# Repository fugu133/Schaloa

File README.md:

# 超小型分光光度計Schaloa
## 概要
浜松ホトニクスのマイクロ分光器[C12880MA](https://www.hamamatsu.com/jp/ja/product/optical-sensors/spectrometers/mini-spectrometer/C12880MA.html)を用いた分光光度計モジュールのハードウェア設計データです．  
本装置を使うと可視領域の分光計測や吸光光度分析がハンディサイズで実現可能です．  
主にCADはEagleとFusionを使用しています．詳しい仕様は[こちら](design_specifications.pdf)    

## 基板のイメージ
### メイン制御基板
分光器や各系の制御，PCとの通信を行います．

### 分光器基板
分光器のブレークアウト基板です．

## 計測デモ
蛍光灯と一般的な白色LEDの放射光スペクトルを計測しました．

### 蛍光灯
405nm，436nm，546nm及び577nm付近に鋭いピークが見られます．  
これらは蛍光灯の発光源である水銀の原子スペクトルと一致しています．  
この光を管内の蛍光体に照射すると蛍光により白色光が作成されます．

### 白色LED
頂点が過剰露出により潰れていますが，440nm付近に鋭いピークが見られます．  
これはパッケージ内部の青色LEDによる光だと考えられます．所謂ブルーライトです．  
また550nm-560nm付近を中心に広いピークを確認できます．  
これは黄色系の蛍光体の蛍光だと考えられます．白色LEDはこのようにして白色光を作成します．

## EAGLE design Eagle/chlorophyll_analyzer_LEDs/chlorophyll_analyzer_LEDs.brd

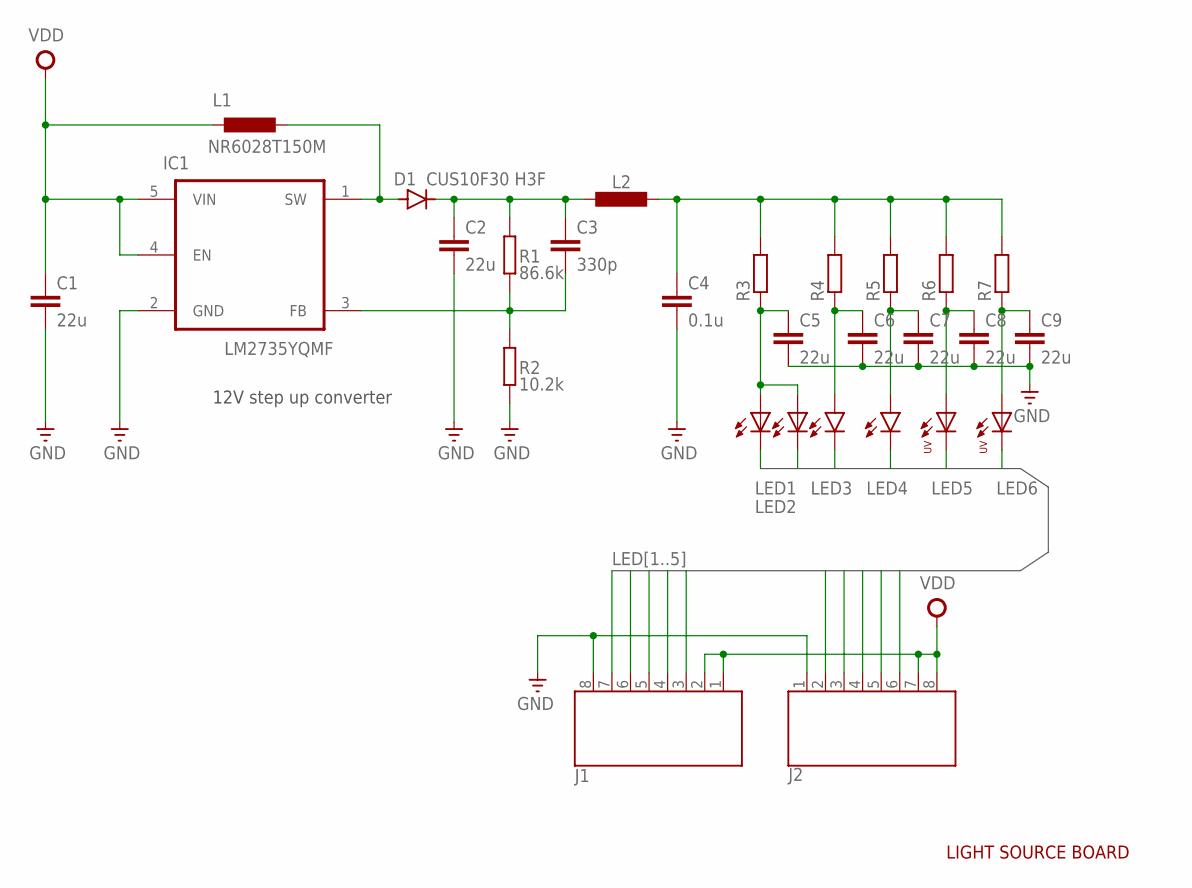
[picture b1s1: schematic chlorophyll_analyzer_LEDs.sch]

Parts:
C1, C2, C5, C6, C7, C8, C9: 22u; C0603K
C3: 330p; C0603K
C4: 0.1u; C0603K
D1: CUS10F30 H3F; SOD323-W
IC1: LM2735YQMF; SOT65P285X120-5N
J1, J2: 687108183722
L1: NR6028T150M; IND_TAIYO_NR6028
L2: INDUCOR2012; SMD2012
LED1, LED2: L130-S1S0-3030509506-0000003S-000015080003000W21; LED_L130-5080003000W21
LED3, LED4: LEDCHIPLED_1206; CHIPLED_1206
LED5, LED6: ELUA2016OGB-P8090Q53038020-VA1M; ELUA2016OGB0.08
R1: 86.6k; SMD1608
R2: 10.2k; SMD1608
R3, R4, R5, R6, R7: R-EU_R0805; R0805

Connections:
AVOUT_12V: C4.1, L2.1, R3.2, R4.2, R5.2, R6.2, R7.2
GND: C1.2, C2.2, C4.2, C5.2, C6.2, C7.2, C8.2, C9.2, IC1.2 (GND), J1.8 (1), J2.1 (8), R2.1
LED1: J1.3 (6), J2.6 (3), LED1.C, LED2.C
LED2: J1.4 (5), J2.5 (4), LED3.C
LED3: J1.5 (4), LED4.C
LED4: J1.6 (3), J2.3 (6), J2.4 (5), LED5.C (C1)
LED5: J1.7 (2), J2.2 (7), LED6.C (C1)
unnamed: C5.1, LED1.A, LED2.A, R3.1
unnamed: C6.1, LED3.A, R4.1
unnamed: C7.1, LED4.A, R5.1
unnamed: C9.1, LED6.A (A1), R7.1
unnamed: C8.1, LED5.A (A1), R6.1
unnamed: C2.1, C3.1, D1.C, L2.2, R1.2
unnamed: D1.A, IC1.1 (SW), L1.1
unnamed: C3.2, IC1.3 (FB), R1.1, R2.2
VDD: C1.1, IC1.4 (EN), IC1.5 (VIN), J1.1 (8), J1.2 (7), J2.7 (2), J2.8 (1), L1.2

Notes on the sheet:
12V step up converter
LIGHT SOURCE BOARD

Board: 2 copper layers, 28 parts (21 on the bottom side), 16 nets, no tracks yet.

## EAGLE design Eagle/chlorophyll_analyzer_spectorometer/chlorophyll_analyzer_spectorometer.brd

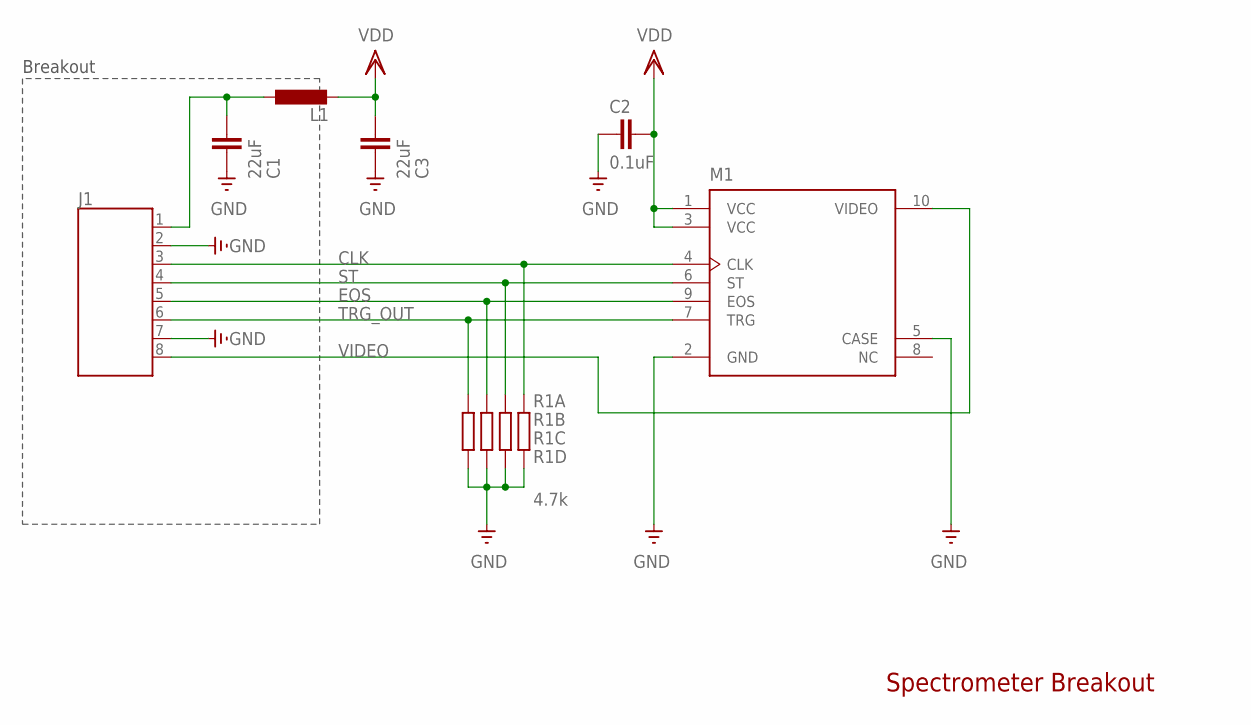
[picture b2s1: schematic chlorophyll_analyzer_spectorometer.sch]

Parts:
C1, C3: 22uF; C0603K
C2: 0.1uF; C0603K
J1: 687108183722
L1: INDUCOR1608; SMD1608
M1: C12880MA
R1: 4.7k; RESCAXS80P320X160X60-8N

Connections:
CLK: J1.3 (6), M1.4 (CLK), R1.5 (2)
EOS: J1.5 (4), M1.9 (EOS), R1.7 (2)
GND: C1.2, C2.2, C3.2, J1.2 (7), J1.7 (2), M1.2 (GND), M1.5 (CASE), R1.1, R1.2 (1), R1.3 (1), R1.4 (1)
unnamed: C1.1, J1.1 (8), L1.1
ST: J1.4 (5), M1.6 (ST), R1.6 (2)
TRG_OUT: J1.6 (3), M1.7 (TRG), R1.8 (2)
VDD: C2.1, C3.1, L1.2, M1.1 (VCC), M1.3 (VCC)
VIDEO: J1.8 (1), M1.10 (VIDEO)

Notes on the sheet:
Breakout
Spectrometer Breakout

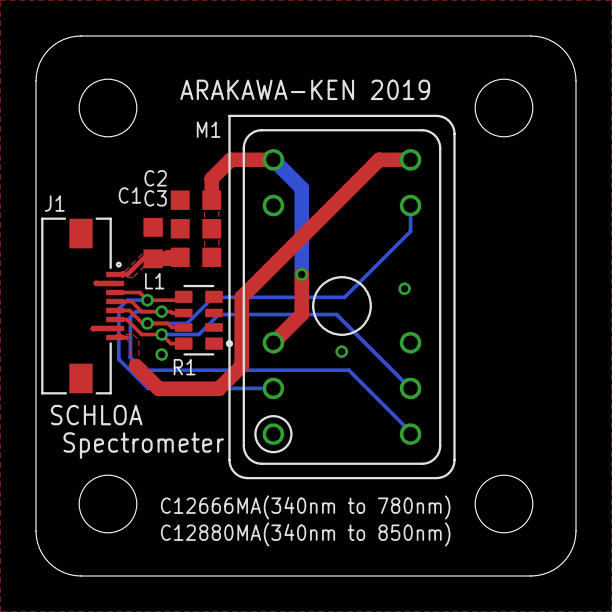
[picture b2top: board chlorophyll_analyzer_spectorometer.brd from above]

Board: 2 copper layers, 30.0 x 30.0 mm, 7 parts (0 on the bottom side), 8 nets.

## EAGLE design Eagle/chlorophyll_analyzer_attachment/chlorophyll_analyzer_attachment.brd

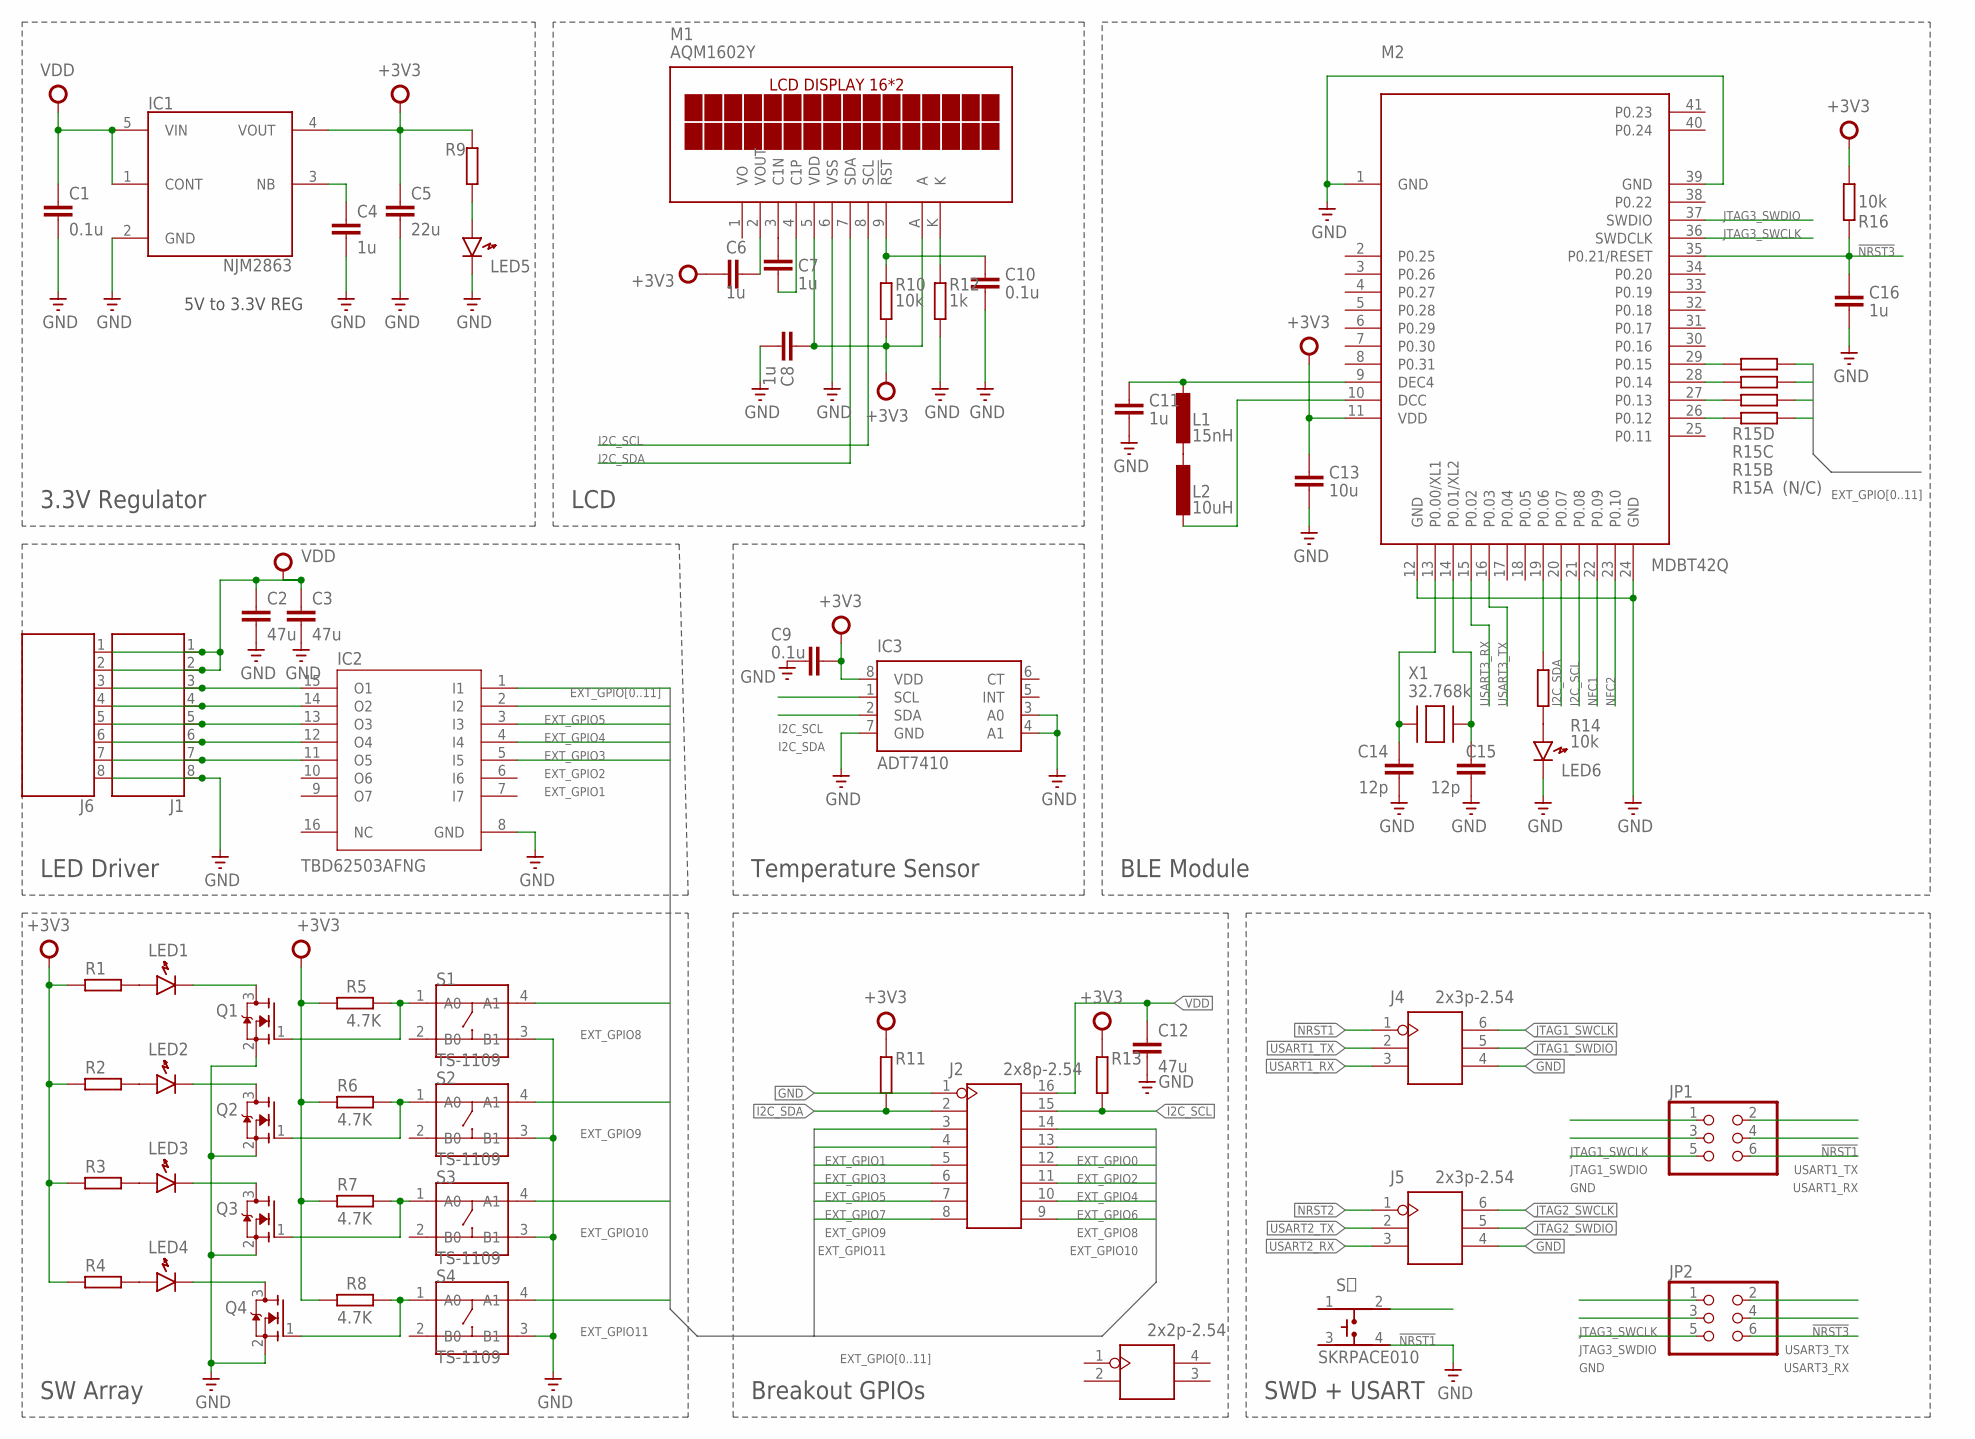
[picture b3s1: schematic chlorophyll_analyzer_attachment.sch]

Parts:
C1, C9, C10: 0.1u; C0603K
C2, C3, C12: 47u; C1206
C4, C6, C7, C8, C11, C16: 1u; C0603K
C5: 22u; C0603K
C13: 10u; C0603K
C14, C15: 12p; C0603K
IC1: NJM2863; SOT-23-5
IC2: TBD62503AFNG; SSOP16-P-225-0.65B
IC3: ADT7410; SOIC8
J1, J6: 687108183722
J2: 2x8p-2.54; H2X8-2.54
J3: 2x2p-2.54; H2X2-2.54
J4, J5: 2x3p-2.54; H2X3-2.54
JP1, JP2: PINHD-2X3; 2X03
L1: 15nH; SMD1608
L2: 10uH; SMD1608
LED1, LED2, LED3, LED4, LED5, LED6: LED1608
M1: AQM1602Y
M2: MDBT42Q
Q1, Q2, Q3, Q4: MOSFET-NREFLOW; SOT23
R1, R2, R3, R4, R9, R11, R13: RESISTOR1608; SMD1608
R5, R6, R7, R8: 4.7K; SMD1608
R10, R14, R16: 10k; SMD1608
R12: 1k; SMD1608
R15: (N/C); RESCAXS80P320X160X60-8N
S1, S2, S3, S4: TS-1109; SW4-6.0X6.0X5.0MM
S５: SKRPACE010; SW_SKRPACE010
X1: 32.768k; XTAL3215

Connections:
!NRST1: J4.1, JP1.2, S５.2
!NRST2: J5.1
!NRST3: C16.1, JP2.2, M2.35 (P0.21/RESET), R16.1
+3V3: C5.1, C6.1, C8.2, C9.1, C13.1, IC1.4 (VOUT), IC3.8 (VDD), M1.5 (VDD), M1.A, M2.11 (VDD), R1.1, R2.1, R3.1, R4.1, R5.1, R6.1, R7.1, R8.1, R9.1, R10.2, R11.1, R13.1, R16.2
EXT_GPIO0: J2.14
EXT_GPIO1: IC2.5 (I5), J2.3
EXT_GPIO2: IC2.4 (I4), J2.13
EXT_GPIO3: IC2.3 (I3), J2.4
EXT_GPIO4: IC2.2 (I2), J2.12
EXT_GPIO5: IC2.1 (I1), J2.5
EXT_GPIO6: J2.11
EXT_GPIO7: J2.6
EXT_GPIO8: J2.10, R15.8 (2), S1.4 (A1)
EXT_GPIO9: J2.7, R15.7 (2), S2.4 (A1)
EXT_GPIO10: J2.9, R15.6 (2), S3.4 (A1)
EXT_GPIO11: J2.8, R15.5 (2), S4.4 (A1)
GND: C1.2, C2.2, C3.2, C4.2, C5.2, C8.1, C9.2, C10.2, C11.2, C12.2, C13.2, C14.2, C15.2, C16.2, IC1.2 (GND), IC2.8 (GND), IC3.3 (A0), IC3.4 (A1), IC3.7 (GND), J1.8 (1), J2.1, J4.4, J5.4, J6.8 (1), JP1.5, JP2.5, LED5.K, LED6.K, M1.6 (VSS), M2.1 (GND), M2.12 (GND), M2.24 (GND), M2.39 (GND), Q1.2 (S), Q2.2 (S), Q3.2 (S), Q4.2 (S), R12.2, S1.3 (B1), S2.3 (B1), S3.3 (B1), S4.3 (B1), S５.4
I2C_SCL: IC3.1 (SCL), J2.15, M1.8 (SCL), M2.21 (P0.08), R13.2
I2C_SDA: IC3.2 (SDA), J2.2, M1.7 (SDA), M2.20 (P0.07), R11.2
JTAG1_SWCLK: J4.6, JP1.1
JTAG1_SWDIO: J4.5, JP1.3
JTAG2_SWCLK: J5.6
JTAG2_SWDIO: J5.5
JTAG3_SWCLK: JP2.1, M2.36 (SWDCLK)
JTAG3_SWDIO: JP2.3, M2.37 (SWDIO)
unnamed: C6.2, M1.2 (VOUT)
unnamed: C7.2, M1.3 (C1N)
unnamed: C7.1, M1.4 (C1P)
unnamed: C4.1, IC1.3 (NB)
unnamed: LED5.A, R9.2
unnamed: C10.1, M1.9 (!RST), R10.1
unnamed: M1.K, R12.1
unnamed: Q1.1 (G), R5.2, S1.1 (A0)
unnamed: Q2.1 (G), R6.2, S2.1 (A0)
unnamed: Q3.1 (G), R7.2, S3.1 (A0)
unnamed: Q4.1 (G), R8.2, S4.1 (A0)
unnamed: L2.2, M2.10 (DCC)
unnamed: M2.19 (P0.06), R14.2
unnamed: C11.1, L1.1, M2.9 (DEC4)
unnamed: LED6.A, R14.1
unnamed: LED1.A, R1.2
unnamed: LED2.A, R2.2
unnamed: LED3.A, R3.2
unnamed: LED4.A, R4.2
unnamed: LED4.K, Q4.3 (D)
unnamed: LED3.K, Q3.3 (D)
unnamed: LED2.K, Q2.3 (D)
unnamed: LED1.K, Q1.3 (D)
unnamed: C14.1, M2.13 (P0.00/XL1), X1.P$1
unnamed: L1.2, L2.1
unnamed: C15.1, M2.14 (P0.01/XL2), X1.P$2
unnamed: M2.26 (P0.12), R15.1
unnamed: M2.27 (P0.13), R15.2 (1)
unnamed: M2.28 (P0.14), R15.3 (1)
unnamed: M2.29 (P0.15), R15.4 (1)
unnamed: IC2.15 (O1), J1.3 (6), J6.3 (6)
unnamed: IC2.14 (O2), J1.4 (5), J6.4 (5)
unnamed: IC2.13 (O3), J1.5 (4), J6.5 (4)
unnamed: IC2.12 (O4), J1.6 (3), J6.6 (3)
unnamed: IC2.11 (O5), J1.7 (2), J6.7 (2)
NFC1: M2.22 (P0.09)
NFC2: M2.23 (P0.10)
USART1_RX: J4.3, JP1.6
USART1_TX: J4.2, JP1.4
USART2_RX: J5.3
USART2_TX: J5.2
USART3_RX: JP2.6, M2.15 (P0.02)
USART3_TX: JP2.4, M2.16 (P0.03)
VDD: C1.1, C2.1, C3.1, C12.1, IC1.1 (CONT), IC1.5 (VIN), J1.1 (8), J1.2 (7), J2.16, J6.1 (8), J6.2 (7)

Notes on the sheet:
SWD + USART
Breakout GPIOs
5V to 3.3V REG
SW Array
LED Driver
Temperature Sensor
BLE Module
3.3V Regulator
LCD

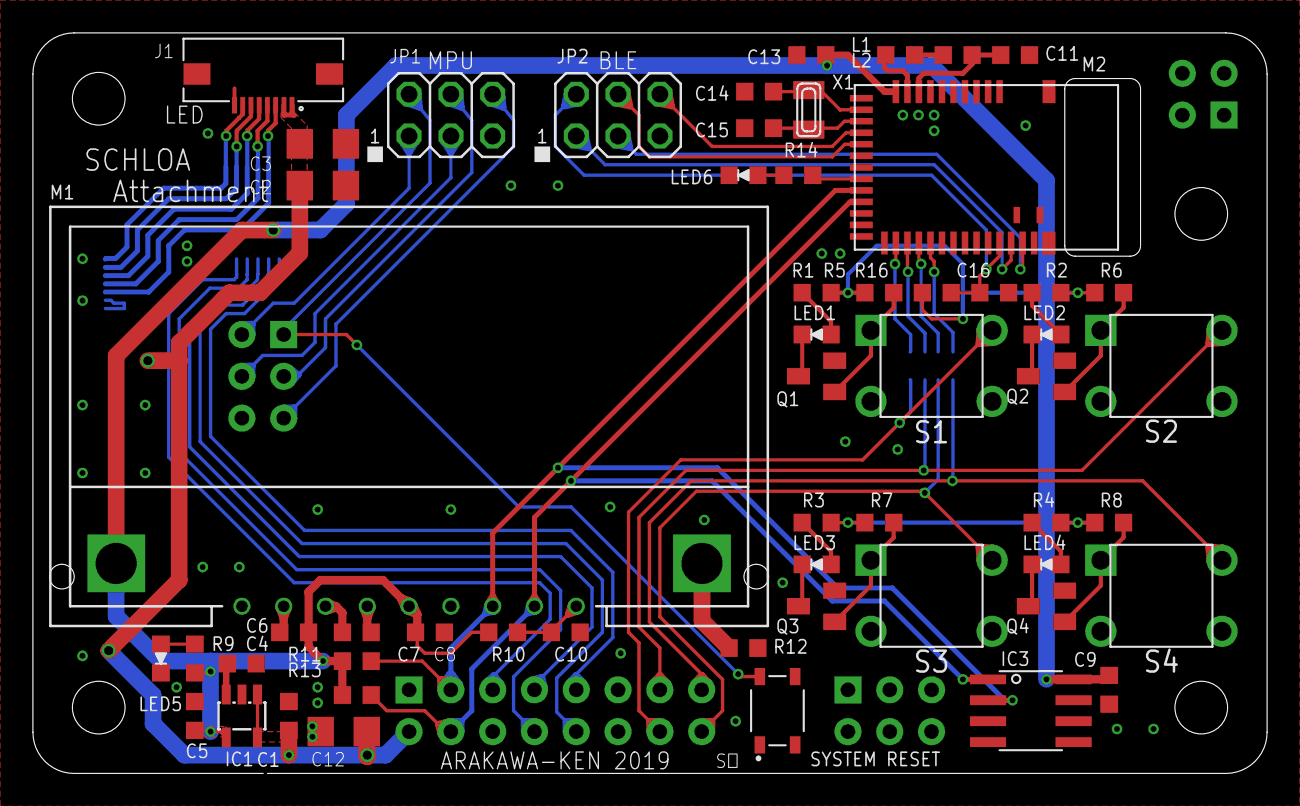
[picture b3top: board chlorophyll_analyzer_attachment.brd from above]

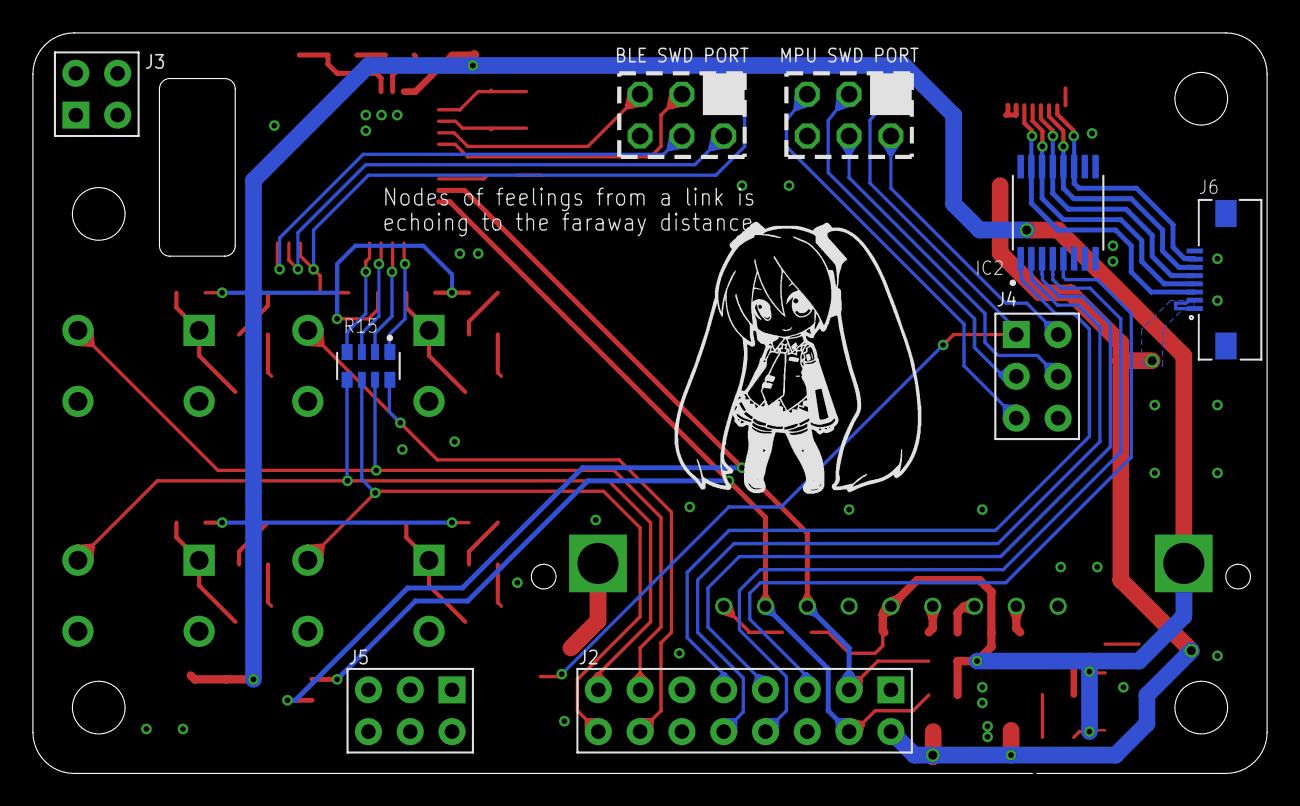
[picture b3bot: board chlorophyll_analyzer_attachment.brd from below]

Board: 2 copper layers, 75.0 x 45.0 mm, 63 parts (7 on the bottom side), 59 nets.

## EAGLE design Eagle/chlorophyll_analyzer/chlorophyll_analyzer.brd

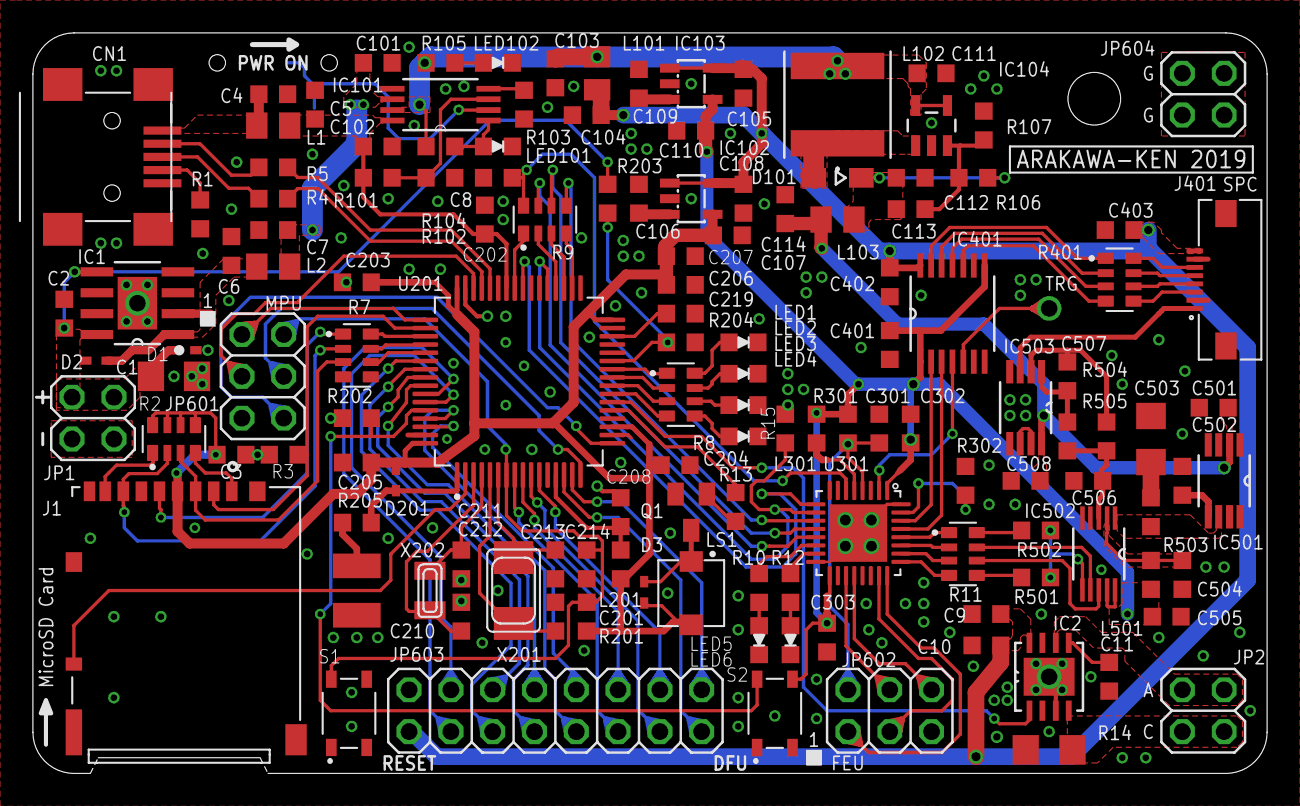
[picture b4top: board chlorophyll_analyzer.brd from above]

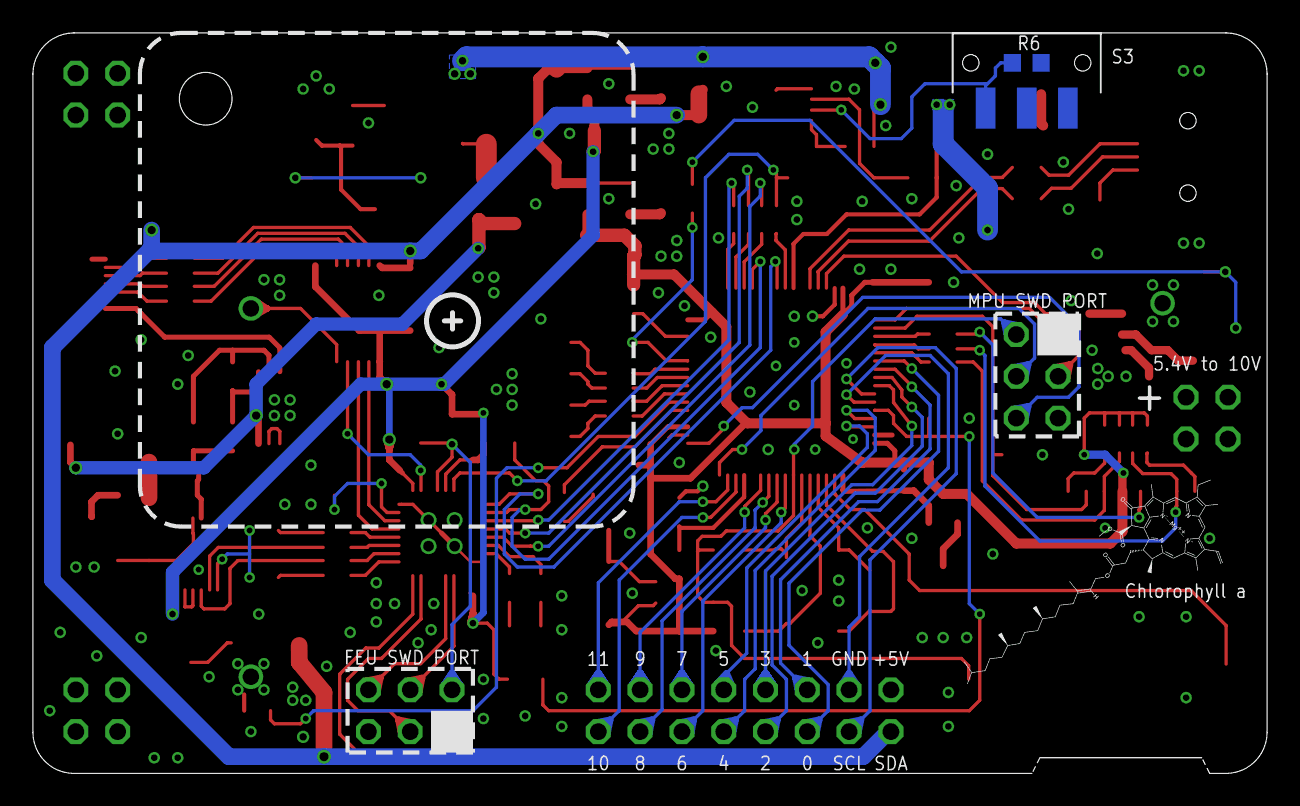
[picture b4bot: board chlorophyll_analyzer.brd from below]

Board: 2 copper layers, 75.0 x 45.0 mm, 137 parts (2 on the bottom side), 130 nets.

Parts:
C1, C503: 47u; C1206
C2, C106, C109, C501, C502, C504, C505: 1u; C0603K
C3, C4, C6, C9, C101, C102, C103, C104, C107, C110, C111, C112: 22u; C0603K
C5, C7, C10, C105, C108, C114, C201, C202, C203, C204, C205, C206, C208, C301, C302, C303, C401, C402, C508: 0.1u; C0603K
C8: 20p; C0603K
C11: 47n; C0603K
C113: 330p; C0603K
C207, C219: 4.7u; C0603K
C210: CPH3225A(11mF); C1210K
C211, C212: 12p; C0603K
C213, C214: 18p; C0603K
C403: 22uF; C0603K
C506, C507: 2.4n; C0603K
CN1: USB-MINIB
D1, D2, D3, D201: RB520S-30; SOD523
D101: CUS10F30 H3F; SOD323-W
IC1: BD50HC5WEFJ; HTSOP-J8
IC2: TL4242DRJR; SON80P410X410X80-9N
IC101: TPS2113PW; SOP65P640X120-8N
IC102, IC103: NJM2863; SOT-23-5
IC104: LM2735YQMF; SOT65P285X120-5N
IC401: TXB0104PWR; SOP65P640X120-14N
IC501: REF5050AIDGKT; SOP65P490X110-8N
IC502: ADS8866IDGS; SOP50P490X110-10N
IC503: OPA2388IDGKT; SOP65P490X110-9N
J1: DM3AT-SF-PEJM5; HRS_DM3AT-SF-PEJM5
J401: 687108183722
JP1, JP2, JP604: 2X02
JP601, JP602: 2X03
JP603: 2X08
L1, L2, L101, L103: SMD2012
L102: NR6028T150M; IND_TAIYO_NR6028
L201, L301, L501: SMD1608
LED1, LED2, LED3, LED4, LED5, LED6, LED101, LED102: LED1608
LS1: SMT-0440-T-R; XDCR_SMT-0440-T-R
Q1: SOT23
R1, R3, R15: 100k; SMD1608
R2: 22k; RESCAXS80P320X160X60-8N
R4, R5: 10; SMD1608
R6, R502: 0(N/C); SMD1608
R7, R9, R11, R401: 20; RESCAXS80P320X160X60-8N
R8: 4.7k; RESCAXS80P320X160X60-8N
R10, R12, R104, R105, R204: 4.7k; SMD1608
R13, R101: 1k; SMD1608
R14: R1206
R102, R201, R202, R203, R301, R302: 10k; SMD1608
R103: 400; SMD1608
R106: 86.6k; SMD1608
R107: 10.2k; SMD1608
R205: 100; SMD1608
R501, R503: 0; SMD1608
R504, R505: 20k; SMD1608
S1, S2: SKRPACE010; SW_SKRPACE010
S3: JS102011SAQN; SW_JS102011SAQN
U201: STM32F446RET6; QFP50P1200X1200X160-64N
U301: STM32L432KCU6; QFN50P500X500X60-33N
X201: 8.0MHz; NX5032
X202: 32.768k; XTAL3215

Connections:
!FEU_NRST: C301.1, JP602.2, R301.2, U301.4
!FEU_SPI_CS: R15.1, U201.37, U301.10
!MPU_NRST: C201.2, JP601.2, R201.2, S1.2, U201.7
!SD_CDETECT: J1.SWA, U201.2
!SD_SPI_CS: J1.2, R3.1, U201.50
+3V3A: C3.1, C107.1, C203.1, C204.1, C205.1, C206.1, C207.1, D3.C, D201.A, IC102.4, J1.4, L201.1, LS1.2, R2.5, R2.6, R2.7, R2.8, R201.1, U201.19, U201.32, U201.48, U201.64
+3V3C: C110.1, C302.1, C303.1, C401.2, C505.1, IC103.4, IC401.1, IC401.8, IC502.9, IC502.10, L301.1, L501.1, R301.1, S2.4, U301.1, U301.17
+5VA: C103.1, C111.1, IC101.7, IC104.4, IC104.5, L101.2, L102.2, R104.1, R105.1
+5VD: C9.2, C10.2, C104.1, C105.1, C108.1, C402.1, C403.1, IC2.8, IC102.1, IC102.5, IC103.1, IC103.5, IC401.14, J401.8, JP603.1, L101.1
+12V: C114.1, C501.1, C508.1, IC501.2, IC503.8, L103.1
ADC_AT_TRG: R11.8, R502.1
ADC_MN_TRG: R11.5, R501.1
ADC_SPI_MISO: IC502.7, R11.7
ADC_SPI_SCLK: IC502.8, R11.6
ADC_UNIT:ADC_CTRG: IC502.6, R501.2, R502.2
ADC_UNIT:N$1: C503.2, R503.1
ADC_UNIT:N$2: IC503.6, IC503.7
ADC_UNIT:N$3: C504.1, IC502.2, L501.2
ADC_UNIT:N$25: C506.1, IC502.3, R504.1, R505.1
ADC_UNIT:N$26: C507.1, IC503.1, R504.2
ADC_UNIT:N$30: C507.2, IC503.2, R505.2
ADC_UNIT:N$34: C502.1, IC501.5
ADC_UNIT:VREF: IC501.6, IC502.1, R503.2
EXT_GPIO0: JP603.5, U201.54
EXT_GPIO1: JP603.6, U201.55
EXT_GPIO2: JP603.7, U201.56
EXT_GPIO3: JP603.8, U201.57
EXT_GPIO4: JP603.9, U201.61
EXT_GPIO5: JP603.10, U201.62
EXT_GPIO6: JP603.11, U201.8
EXT_GPIO7: JP603.12, U201.9
EXT_GPIO8: JP603.13, U201.10
EXT_GPIO9: JP603.14, U201.11
EXT_GPIO10: JP603.15, U201.14
EXT_GPIO11: JP603.16, U201.15
FEU_MCLK: C8.1, R9.8, U301.6
FEU_RX: JP602.6, U301.20
FEU_SPI_BUSY: U201.40, U301.9
FEU_SPI_SCLK: R9.5, U301.11
FEU_ST_LED0: R10.1, U301.14
FEU_ST_LED1: R12.1, U301.15
FEU_SWCLK: JP602.1, U301.24
FEU_SWDIO: JP602.3, U301.23
FEU_TX: JP602.4, U301.19
FPU_SPI_MISO: R9.6, U301.12
FPU_SPI_MOSI: R9.7, U301.13
FRONT_END_UNIT:N$1: L301.2, U301.5
FRONT_END_UNIT:N$10: R302.1, U301.31
GND: C1.2, C2.2, C3.2, C4.2, C5.2, C6.2, C7.2, C8.2, C9.1, C10.1, C11.1, C101.2, C102.2, C103.2, C104.2, C105.2, C106.2, C107.2, C108.2, C109.2, C110.2, C111.2, C112.2, C114.2, C201.1, C202.1, C203.2, C204.2, C205.2, C206.2, C207.2, C208.2, C210.2, C211.2, C212.2, C213.2, C214.2, C219.2, C301.2, C302.2, C303.2, C401.1, C402.2, C403.2, C501.2, C502.2, C503.1, C504.2, C505.2, C506.2, C508.2, CN1.GND, CN1.GND1, CN1.GND2, CN1.GND3, CN1.GND4, D1.A, IC1.3, IC1.4, IC1.6, IC1.7, IC1.9, IC2.3, IC2.9, IC101.5, IC102.2, IC103.2, IC104.2, IC401.7, IC501.4, IC502.4, IC502.5, IC503.4, IC503.5, J1.6, J1.P1, J1.P2, J1.P3, J1.P4, J1.SWB, J401.2, J401.7, JP1.3, JP1.4, JP601.5, JP602.5, JP603.2, JP604.1, JP604.2, JP604.3, JP604.4, LED1.K, LED2.K, LED3.K, LED4.K, LED5.K, LED6.K, LED101.K, LED102.K, Q1.2, R1.2, R3.2, R6.1, R14.1, R15.2, R102.2, R103.2, R107.1, R202.1, R204.1, R302.2, S1.4, S3.2, U201.12, U201.18, U201.31, U201.47, U201.63, U301.16, U301.32, U301.33
LED_PWM_OUT: IC2.1, U201.22
MAIN_PROCESSING_UNIT:EXT_CLK: C214.1, U201.5, X201.P$1
MAIN_PROCESSING_UNIT:N$1: C219.1, U201.30
MAIN_PROCESSING_UNIT:N$2: C212.1, U201.3, X202.P$2
MAIN_PROCESSING_UNIT:N$3: C208.1, L201.2, U201.13
MAIN_PROCESSING_UNIT:N$4: D201.C, R205.1, U201.1
MAIN_PROCESSING_UNIT:N$6: C211.1, U201.4, X202.P$1
MAIN_PROCESSING_UNIT:N$9: C213.1, U201.6, X201.P$2
MAIN_PROCESSING_UNIT:N$11: R203.1, R204.2, U201.27
MAIN_PROCESSING_UNIT:N$12: C210.1, R205.2
MPU_DFU: R202.2, S2.2, U201.60
MPU_RX: JP601.6, U201.17
MPU_SCL: JP603.3, U201.58
MPU_SDA: JP603.4, U201.59
MPU_ST_LED0: R8.1, U201.26
MPU_ST_LED1: R8.2, U201.25
MPU_ST_LED2: R8.3, U201.24
MPU_ST_LED3: R8.4, U201.23
MPU_SWCLK: JP601.1, U201.49
MPU_SWDIO: JP601.3, U201.46
MPU_TX: JP601.4, U201.16
unnamed: LED1.A, R8.8
unnamed: LED2.A, R8.7
unnamed: LED3.A, R8.6
unnamed: LED4.A, R8.5
unnamed: J1.8, R2.1
unnamed: J1.1, R2.4
unnamed: C6.1, D2.A, IC1.1, IC1.2, L2.2
unnamed: LED5.A, R10.2
unnamed: Q1.1, R13.2
unnamed: C4.1, CN1.VBUS, L1.2
unnamed: IC101.2, R6.2, S3.3
unnamed: LED6.A, R12.2
unnamed: C11.2, IC2.5
unnamed: D3.A, LS1.1, Q1.3
unnamed: R9.4, U201.34
unnamed: C7.1, C101.1, IC101.6, L2.1
unnamed: R7.8, U201.51
unnamed: R7.6, U201.53
unnamed: IC2.4, JP2.3, JP2.4, R14.2
unnamed: IC503.3, J401.1
unnamed: R7.7, U201.52
unnamed: R9.2, U201.36
unnamed: R9.3, U201.35
unnamed: R9.1, U201.41
unnamed: R11.1, U301.28
unnamed: R11.2, U301.27
unnamed: R11.3, U301.26
unnamed: R11.4, U301.25
unnamed: CN1.ID, R1.1
POWER_LED_OUT: IC2.6, JP2.1, JP2.2
POWER_UNIT:N$2: IC101.3, R101.2, R102.1
POWER_UNIT:N$3: IC101.4, R103.1
POWER_UNIT:N$4: C106.1, IC102.3
POWER_UNIT:N$5: LED102.A, R105.2
POWER_UNIT:N$6: C109.1, IC103.3
POWER_UNIT:N$7: C112.1, C113.1, D101.C, L103.2, R106.2
POWER_UNIT:N$8: D101.A, IC104.1, L102.1
POWER_UNIT:N$9: C113.2, IC104.3, R106.1, R107.2
POWER_UNIT:SUP_CH_STAT1: IC101.1, LED101.A, R104.2
SD_SPI_MISO: J1.7, R2.2, R7.2
SD_SPI_MOSI: J1.3, R2.3, R7.3
SD_SPI_SCLK: J1.5, R7.1
SOUND_OUT: R13.1, U201.21
SPC_EOS: IC401.4, U301.2
SPC_SCLK: IC401.2, U301.30
SPC_ST: IC401.3, U301.29
SPECTROMETER_UNIT:N$1: IC401.13, R401.1
SPECTROMETER_UNIT:N$2: IC401.12, R401.2
SPECTROMETER_UNIT:N$3: IC401.11, R401.3
SPECTROMETER_UNIT:N$4: IC401.10, R401.4
SPECTROMETER_UNIT:N$5: J401.6, R401.8
SPECTROMETER_UNIT:N$6: J401.5, R401.7
SPECTROMETER_UNIT:N$7: J401.4, R401.6
SPECTROMETER_UNIT:N$8: J401.3, R401.5
USBC_N: CN1.D-, R5.1
USBC_P: CN1.D+, R4.1
USB_N: R5.2, U201.44
USB_P: R4.2, U201.45
VBAT: C1.1, C2.1, D1.C, D2.C, IC1.5, IC1.8, JP1.1, JP1.2, R203.2
VUSB: C5.1, C102.1, C202.2, IC101.8, L1.1, R101.1, U201.42

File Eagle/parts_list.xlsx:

|  |  |  | セラミックコンデンサ
部品番号ブヒンバンゴウ | 品名ヒンメイ | 部品定数ブヒンテイスウ | メーカー | 品番ヒンバン
C211, C212 | セラミックコンデンサ | 50V 12pF | muRata | GRM1882C1H120JA01
C8, C213, C214 | セラミックコンデンサ | 50V 18pF | muRata | GRM1882C1H180JA01
C113 | セラミックコンデンサ | 50V 330pF | muRata | GRM1882C1H331JA01
C506, C507 | セラミックコンデンサ | 50V 2.4nF | muRata | GRM1885C1H242JA01D
C11 | セラミックコンデンサ | 50V 47nF | muRata | GCM188R71H473KA55D
C5, C7, C10, C105, C108, C114, C201, C202, C203, C204, C205, C206, C207, C208, 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 | セラミックコンデンサ | 50V 0.1uF | muRata | CM105W5R103K50VAT
C106, C109, C501, C502, C504, C505 | セラミックコンデンサ | 10V 1uF | muRata | GRM188R6YA106MA73
C207, C219 | セラミックコンデンサ | 10V 4.7uF | muRata | GRM188F11A475ZE20
C3, C4, C9, C101, C102, C103, C104, C107, C110, C111, C112, C403 | セラミックコンデンサ | 10V 22uF | muRata | GRM188R61A226ME
C1, C11, C503 | セラミックコンデンサ | 10V 47uF | muRata | GRM31CB31A476KE15
C210 | セラミックコンデンサ | 3.3V 11mF | Seiko | CPH3225A
CN1 | USB miniB コネクタ | USB miniB | HIROSE | MUSB-5B-NE-S175
D1, D2, D3, D201 | ショットキーバリアダイオード | 30V 200mA | ROHM | RB520S-30
D101 | ショットキーバリアダイオード | 30V 1A | TOSHIBA | CUS10F30 H3F
IC1 | リニアレギュレータ | 5V 1.5A | ROHM | BD50HC5WEFJ-E2
IC2 | リニアLEDドライバ | 500mA 1ch | TI | TL4242DRJR
IC101 | パワーマルチプレクサ | 1.25A 2:1 | TI | TPS2113PW
IC102, IC103 | リニアレギュレータ | 3.3V 100mA | New JRC | NJM2863F33
IC104 | DC/DCスイッチングレギュレータ | ADJ 2.1A | TI | LM2735YQMF
IC501 | リファレンス電源デンゲン | 5V 0.1％ | TI | REF5050AIDGKT
IC502 | SAR A/Dコンバータ | 16bit 1ch | TI | ADS8866IDGS
IC503 | 高精度スーパーβオペアンプコウセイド | 2ch | TI | OPA2210IDGKT
J1 | MicroSDC コネクタ | micro SDC | HIROSE | DM3AT-SF-PEJM5
JP1, JP2, JP601 JP602, JP603, JP604 | 2列ピンヘッダレツ | 3A 2.54mm | Usecconn | PH-2x40SG
L1, L2, L101, L103 | フェライトビーズ | 330Ω | muRata | BLM21PG331SN
L201, L301, L501 | フェライトビーズ | 600Ω | muRata | BK2125HS601-T
L102 | パワーインダクタ | 15uH 1.8A | TAIYO | NR6028T150M
LED1, LED3, LED5 | 高輝度LEDコウキド | Blue | ROHM | SMLE13BC8TT86
LED2, LED4, LED6 | 高輝度LEDコウキド | Green | ROHM | SML-E12P8WT86
LED101 | LED | Red | OptoSupply | OSHR1608C1A
LED102 | LED | Orange | OptoSupply | OSOR1608C1A
LS1 | トランスデューサ | 3V 90mA | PUI Audio | XDCR_SMT-0440-T-R
Q1 | Nch MOSFET | 50V 300mA | PANJIT | BSS138
R501, R503 | 抵抗器テイコウキ | 0Ω 1A | KOA | RK73Z1JTTD
R4,R5 | 抵抗器テイコウキ | 10Ω 1/10W | FAITHFUL LINK | RC0603J10R
R7, R9, R11, R401 | 抵抗器アレイテイコウキ | 10Ω 1/10W 4ch | Panasonic | EXB-38V100JV
R205 | 抵抗器テイコウキ | 100Ω 1/10W | FAITHFUL LINK | RC0603J100R
R103 | 薄膜抵抗器ハクマクテイコウキ | 402Ω 1/10W | YAGEO | RT0603DRD07402RL
R13,R101 | 抵抗器テイコウキ | 1kΩ 1/10W | FAITHFUL LINK | RC0603J1K
R8 | 抵抗器アレイテイコウキ | 4.7kΩ 1/10W 4ch | Panasonic | EXB-38V472JV
R8, R10, R104, R105, R204 | 抵抗器テイコウキ | 4.7kΩ 1/10W | FAITHFUL LINK | RC0603J4K7
R102, R201, R202, R203, R301, R302 | 抵抗器テイコウキ | 10kΩ 1/10W | FAITHFUL LINK | RC0603J10K
R107 | 薄膜抵抗器ハクマクテイコウキ | 10.2kΩ 1/10W | YAGEO | RT0603DRE0710K2L
R504, R505 | 薄膜抵抗器ハクマクテイコウキ | 20kΩ 1/10W | YAGEO | RT0603FRE0720KL
R2 | 抵抗器アレイテイコウキ | 22kΩ 1/10W 4ch | Panasonic | EXB-38V223JV
R106 | 薄膜抵抗器ハクマクテイコウキ | 86.6kΩ 1/10W | YAGEO | RT0603DRD0786K6L
R1, R3, R15, | 抵抗器テイコウキ | 100kΩ 1/10W | FAITHFUL LINK | RC0603J100K
S1, S2 | タクトスイッチ | 16V 50mA | ALPS | SKRPACE010
S3 | スライドスイッチ | 6V 300mA | C&K | JS102011SAQN
U201 | Arm マイコン | 32bit 512kByte | STMicro | STM32F446RET6
U301 | Arm マイコン | 32bit 256kByte | STMicro | STM32L432KCU6
X201 | 水晶発振子スイショウハッシンシ | 8.00MHz | Kyocera | CX5032GB08000H0HPQZ1
X202 | 水晶発振子スイショウハッシンシ | 32.768kHz | Kyocera | ST3215SB32768H5HPWAA

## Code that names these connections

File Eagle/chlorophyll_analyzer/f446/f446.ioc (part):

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Mcu.Name=STM32F446R(C-E)Tx
Mcu.Package=LQFP64
Mcu.UserName=STM32F446RETx
PA0-WKUP.GPIOParameters=GPIO_Label
PA0-WKUP.GPIO_Label=EXT_GPIO10
PA0-WKUP.Signal=GPIO_Output
PA1.GPIOParameters=GPIO_Label
PA1.GPIO_Label=EXT_GPIO11
PA1.Signal=GPIO_Output
PA11.Signal=USB_OTG_FS_DM
PA12.Signal=USB_OTG_FS_DP
PA13.Signal=SYS_JTMS-SWDIO
PA14.Signal=SYS_JTCK-SWCLK
PA15.GPIOParameters=GPIO_Label
PA15.GPIO_Label=SPI3_CS
PA15.Signal=GPIO_Output
PA2.Signal=USART2_TX
PA3.Signal=USART2_RX
PA4.Signal=COMP_DAC1_group
PA5.Signal=COMP_DAC2_group
PA7.GPIOParameters=GPIO_Label
PA7.GPIO_Label=INT_GPIO3
PA7.Signal=GPIO_Output
PA8.Mode=Clock-out-1
PA8.Signal=RCC_MCO_1
PA9.Signal=USB_OTG_FS_VBUS
PB0.GPIOParameters=GPIO_Label
PB0.GPIO_Label=INT_GPIO0
PB0.Signal=GPIO_Output
PB1.Signal=ADCx_IN9
PB13.Signal=SPI2_SCK
PB14.Signal=SPI2_MISO
PB15.Signal=SPI2_MOSI
PB3.GPIOParameters=GPIO_Label
PB3.GPIO_Label=EXT_GPIO1
PB3.Signal=GPIO_Output
PB4.GPIOParameters=GPIO_Label
PB4.GPIO_Label=EXT_GPIO2
PB4.Signal=GPIO_Output
PB5.GPIOParameters=GPIO_Label
PB5.GPIO_Label=EXT_GPIO3
PB5.Signal=GPIO_Output
PB6.Mode=I2C
PB6.Signal=I2C1_SCL
PB7.Mode=I2C
PB7.Signal=I2C1_SDA
PB8.GPIOParameters=GPIO_Label
PB8.GPIO_Label=EXT_GPIO4
PB8.Signal=GPIO_Output
PB9.GPIOParameters=GPIO_Label
PB9.GPIO_Label=EXT_GPIO5
PB9.Signal=GPIO_Output
PC0.GPIOParameters=GPIO_Label
PC0.GPIO_Label=EXT_GPIO6
PC0.Signal=GPIO_Output
PC1.GPIOParameters=GPIO_Label
PC1.GPIO_Label=EXT_GPIO7
PC1.Signal=GPIO_Output
PC10.Signal=SPI3_SCK
PC11.Signal=SPI3_MISO
PC12.Signal=SPI3_MOSI
PC14-OSC32_IN.Signal=RCC_OSC32_IN
PC15-OSC32_OUT.Signal=RCC_OSC32_OUT
PC2.GPIOParameters=GPIO_Label
PC2.GPIO_Label=EXT_GPI8
PC2.Signal=GPIO_Output
PC3.GPIOParameters=GPIO_Label
PC3.GPIO_Label=EXT_GPIO9
PC3.Signal=GPIO_Output
PC4.GPIOParameters=GPIO_Label
PC4.GPIO_Label=INT_GPIO2
PC4.Signal=GPIO_Output
PC5.GPIOParameters=GPIO_Label
PC5.GPIO_Label=INT_GPIO1
PC5.Signal=GPIO_Output
PC6.GPIOParameters=GPIO_Label
PC6.GPIO_Label=SPI2_BUSY
PC6.Signal=GPIO_Input
PC7.GPIOParameters=GPIO_Label
PC7.GPIO_Label=SPI2_CS
PC7.Signal=GPIO_Output
PC9.Mode=Clock-out-2
PC9.Signal=RCC_MCO_2
PD2.GPIOParameters=GPIO_Label
PD2.GPIO_Label=EXT_GPIO0
PD2.Signal=GPIO_Output
PH0-OSC_IN.Signal=RCC_OSC_IN
PH1-OSC_OUT.Signal=RCC_OSC_OUT
board=custom

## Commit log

2023-02-28 ハードウェア設計ファイルを追加
2023-03-02 不要ファイルを削除
2023-03-02 Update README.md
    デモを追加
2023-03-14 文章修正

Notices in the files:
parts and their libraries:
Eagle_FPC_CONNECTOR_AND_FFC_CAB: Copyright: Würth Elektronik
